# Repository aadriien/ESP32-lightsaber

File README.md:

# 🪐🤺 Lightsaber

## Description

Introducing... a homemade **lightsaber**, powered by an ESP32 microcontroller! 

This project is still a **work in progress**, so please hang tight while I get things going.

## How It Works

Start by clicking the joystick. This will activate the lightsaber with a cool sound effect (lightspeed)! 

Maneuver the joystick to move between colors. Once you've found a color you like, hold that spot / angle, and click the joystick as you would a button. Keep your ears open for a themed sound corresponding to that specific color! 

To change the blade's hue, angle the joystick button, give it another click, and you'll have returned to "color selection mode". 

When you're ready to deactivate the lightsaber, simply click the joystick again and watch as the lights recede. Listen closely for a message as you go!

## Electronics / Pieces

1. **ESP32-WROOM-32**: microcontroller (logic)
2. **Addressable LED strip (WS2812B)**: lightsaber blade
    - individual LED manipulation 
    - actuator — output
3. **Joystick module**: lightsaber (de)activation
    - range of x, y values to map (+ button)
    - sensor — input
4. **9V battery + clip**: power source
5. **Power supply module**: 5V / 3.3V output converter
6. **Others ad hoc**: cables, wires, resistors, etc

## Tools / Tech

1. **C++**: code running on device
2. **Python**: code to play themed sounds
    - connects via serial monitor
    - using `playsound` library
    - with `PyObjC` to run efficiently
3. **PlatformIO**: embedded development toolset
    - VS Code extension
    - cross-platform, cross-architecture
    - debugger, static analysis, unit testing, etc
    - project configs (build env, dependencies)

## Features

- **⭐️ Lightsaber (de)activation**: Exciting visual effects with sequential LEDs.
- **🎨 Customizable saber blade**: Highly flexible color wheel selection via joystick.

- **🔒 Color locking ability**: Option to hold selected color in place with joystick button.
- **🎵 Themed sound effects**: Music and phrases to match colors and saber (de)activation.

## Video Demos

## Example Images

🎮 Wiring View   |   🌈 Lightsaber LED Strip   |   🔌 Wiring Above
:-------------------------:|:-------------------------:|:-------------------------:
  |    |

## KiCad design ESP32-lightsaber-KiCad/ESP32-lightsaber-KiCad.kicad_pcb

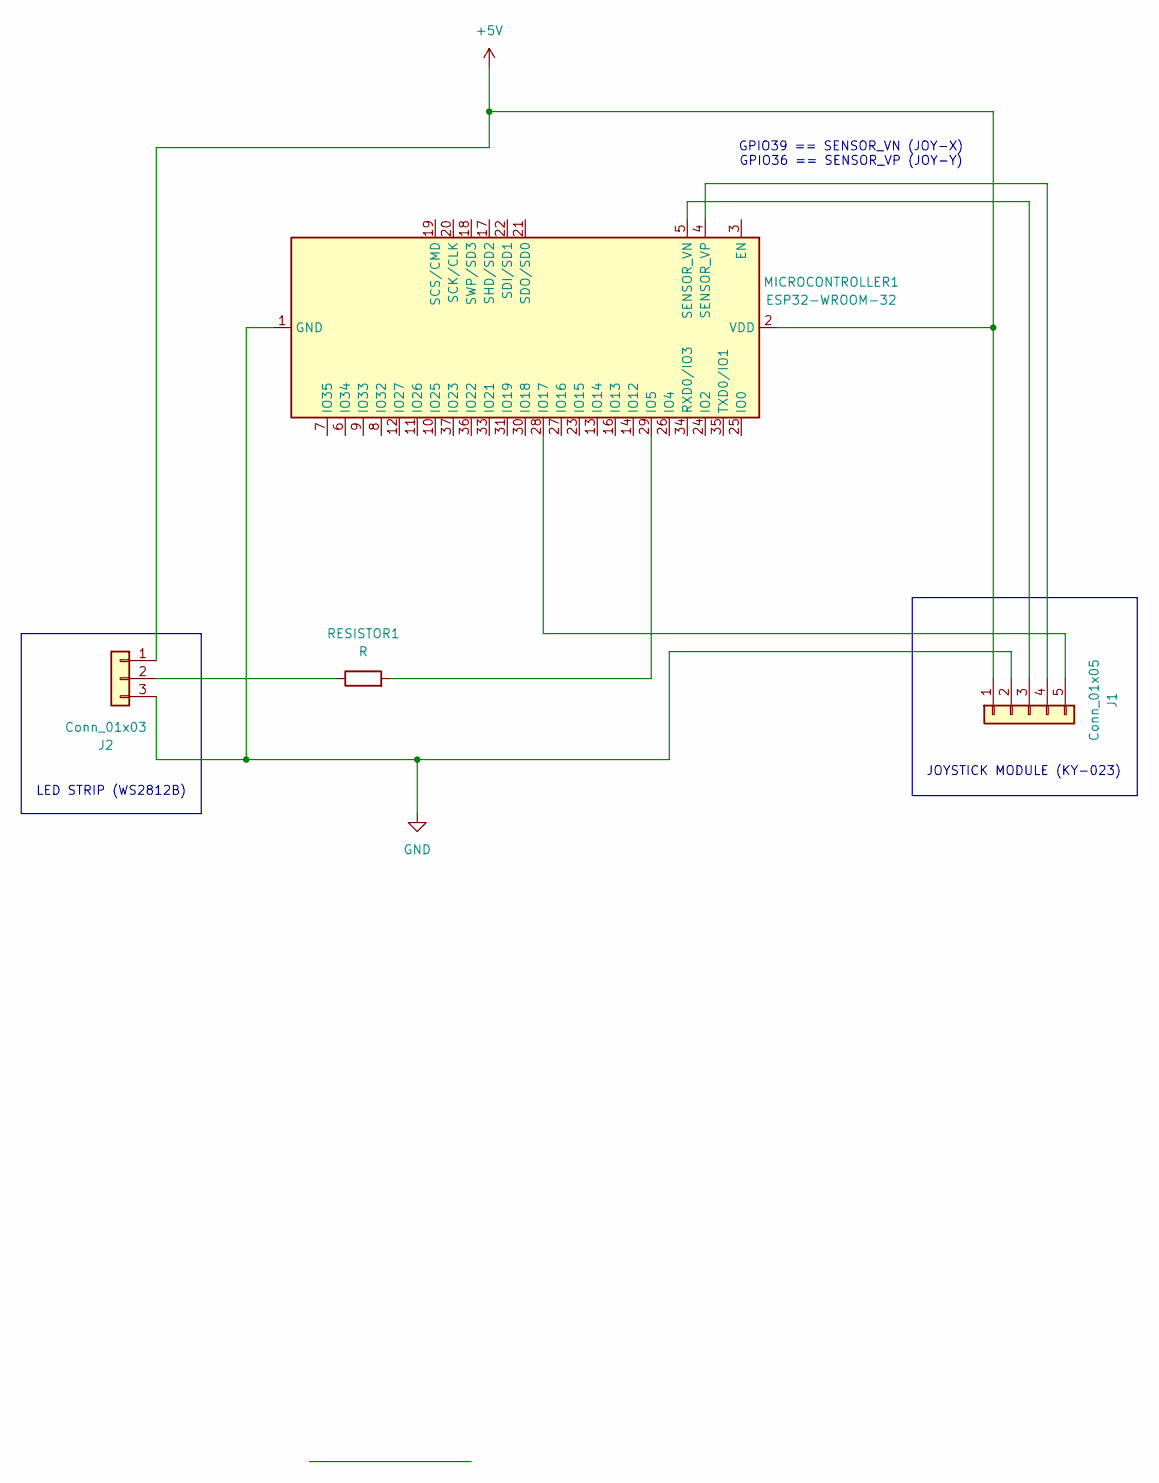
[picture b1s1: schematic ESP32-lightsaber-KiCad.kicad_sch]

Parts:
J1: Conn_01x05; PinHeader_1x05_P2.54mm_Vertical
J2: Conn_01x03; PinHeader_1x03_P2.54mm_Vertical
MICROCONTROLLER1: ESP32-WROOM-32
RESISTOR1: R; R_0805_2012Metric

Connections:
+5V: J1.1, J2.1, MICROCONTROLLER1.2 (VDD)
GND: J1.2, J2.3, MICROCONTROLLER1.1 (GND), MICROCONTROLLER1.15 (GND), MICROCONTROLLER1.38 (GND), MICROCONTROLLER1.39 (GND)
unnamed: J1.3, MICROCONTROLLER1.5 (SENSOR_VN)
unnamed: J1.4, MICROCONTROLLER1.4 (SENSOR_VP)
unnamed: J1.5, MICROCONTROLLER1.28 (IO17)
unnamed: J2.2, RESISTOR1.1
unnamed: MICROCONTROLLER1.29 (IO5), RESISTOR1.2

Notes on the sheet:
LED STRIP (WS2812B)
GPIO39 == SENSOR_VN (JOY-X) GPIO36 == SENSOR_VP (JOY-Y)
JOYSTICK MODULE (KY-023)

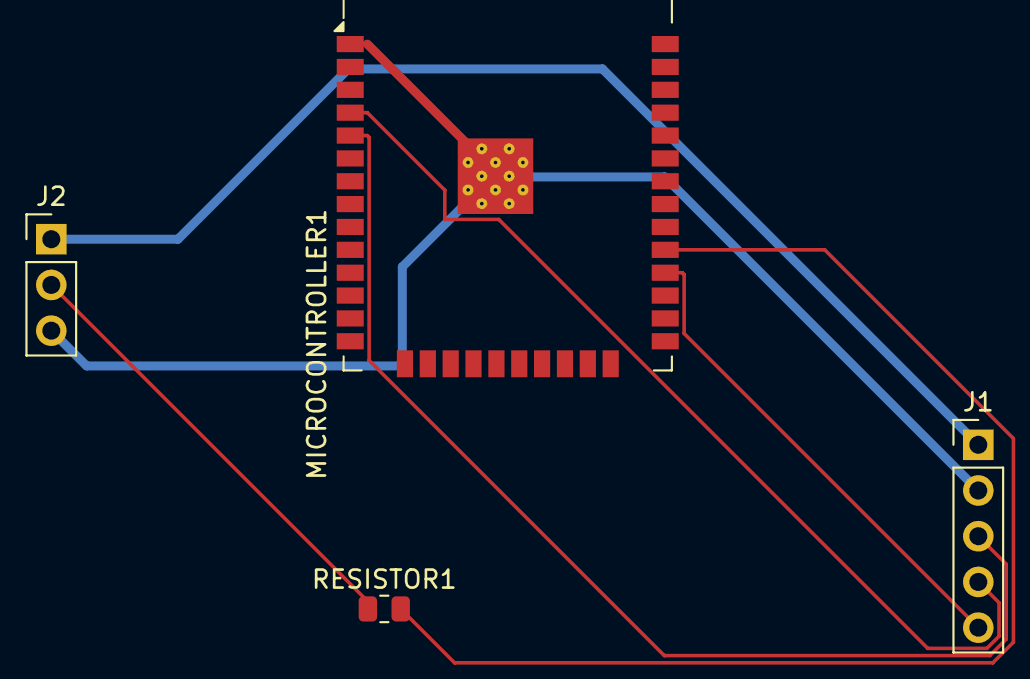
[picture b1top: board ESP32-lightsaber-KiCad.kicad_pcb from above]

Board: 2 copper layers, 4 parts (0 on the bottom side), 7 nets.

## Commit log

2025-06-10 Began with example sketch from FastLED library
2025-06-10 Drafted code for lightsaber activation & deactivation
2025-06-10 Integrated joystick controls for color changes
2025-06-10 Made lightsaber color highly customizable (+ lockable!) via joystick input
2025-06-12 Migrated project into PlatformIO IDE for cleaner dev process
2025-06-12 Fixed indentation following migration
2025-06-12 Integrated sound playing effects with lightsaber color changing
2025-06-12 Fleshed out various sounds for lightsaber colors & activation
2025-06-23 Drafted README.md & shared some example media (photos + gif)
2025-06-23 Reduced file size of gif to mitigate load
2025-06-27 Expanded on use of Python in project, & also compressed gif
2025-06-27 Adjusted sizing & quality of example media / demos
2025-07-11 Updated sound files path for flexibility
2025-07-11 Drafted KiCad schematic for lightsaber circuitry
2025-07-19 Drafted PCB prototype in KiCad from schematic
2025-08-06 Modified lightsaber schematic & PCB following prototype feedback
2025-08-06 Thickened wires for 5V+ power & GND in PCB prototype for current flow
